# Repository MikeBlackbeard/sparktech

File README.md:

# sparktech Group for Hardware Engineering and Embedded Systems

## Team Members
1. Miguel
2. Nur
3. Wen
4. Vincent

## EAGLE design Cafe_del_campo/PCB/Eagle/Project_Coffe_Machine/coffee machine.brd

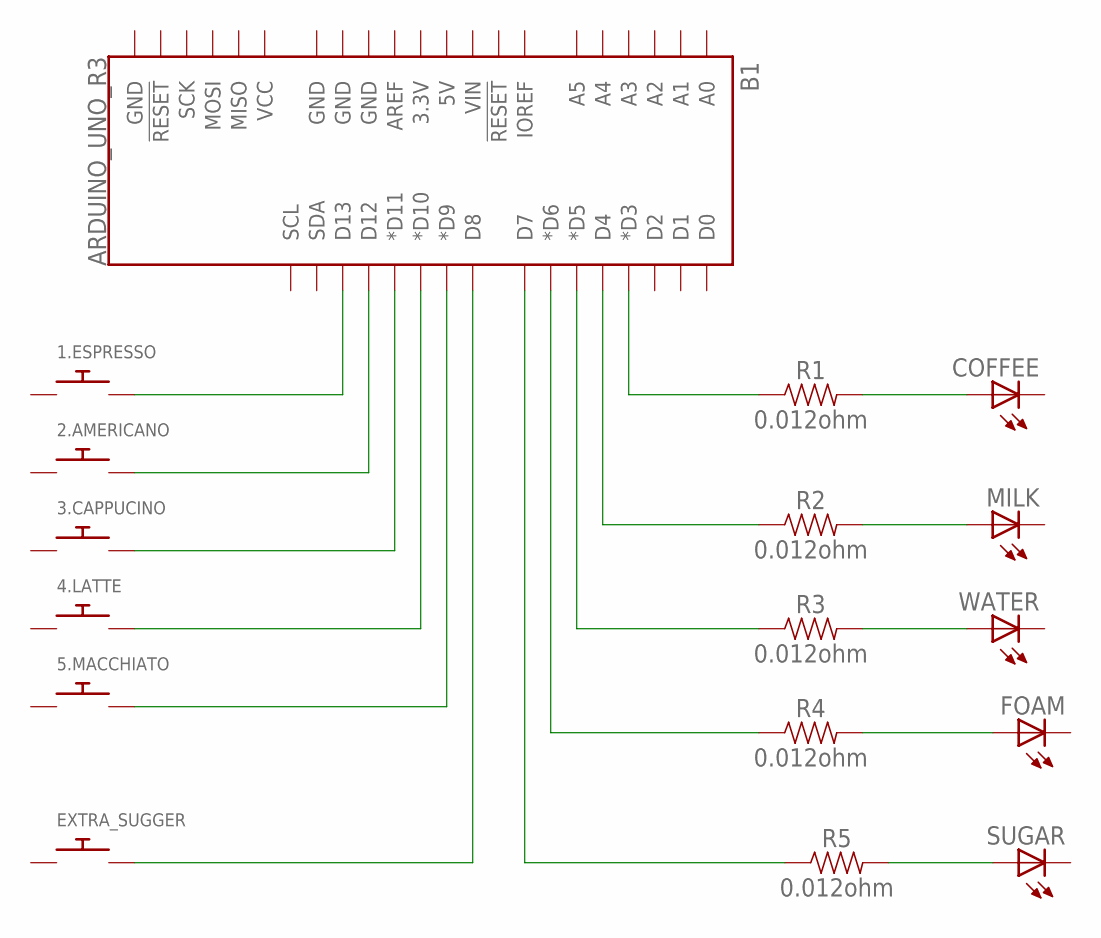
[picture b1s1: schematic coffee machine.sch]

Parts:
1.ESPRESSO, 2.AMERICANO, 3.CAPPUCINO, 4.LATTE, 5.MACCHIATO: SWITCH_PUSHBUTTONEVQ-PE; TACT_PANA-EVQ
B1: ARDUINO_UNO_R3; ARDUINO_R3
COFFEE: LED3MM
EXTRA_SUGGER: SWITCH_PUSHBUTTONEVQ-PE; TACT_PANA-EVQ
FOAM: LED3MM
MILK: LED3MM
R1, R2, R3, R4, R5: 0.012ohm; 0603
SUGAR: LED3MM
WATER: LED3MM

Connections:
unnamed: 1.ESPRESSO.P$2, B1.D13
unnamed: 2.AMERICANO.P$2, B1.D12
unnamed: 3.CAPPUCINO.P$2, B1.D11 (*D11)
unnamed: 4.LATTE.P$2, B1.D10 (*D10)
unnamed: 5.MACCHIATO.P$2, B1.D9 (*D9)
unnamed: B1.D8, EXTRA_SUGGER.P$2
unnamed: B1.D7, R5.1
unnamed: B1.D6 (*D6), R4.1
unnamed: B1.D5 (*D5), R3.1
unnamed: B1.D4, R2.1
unnamed: B1.D3 (*D3), R1.1
unnamed: COFFEE.A, R1.2
unnamed: MILK.A, R2.2
unnamed: R3.2, WATER.A
unnamed: FOAM.A, R4.2
unnamed: R5.2, SUGAR.A

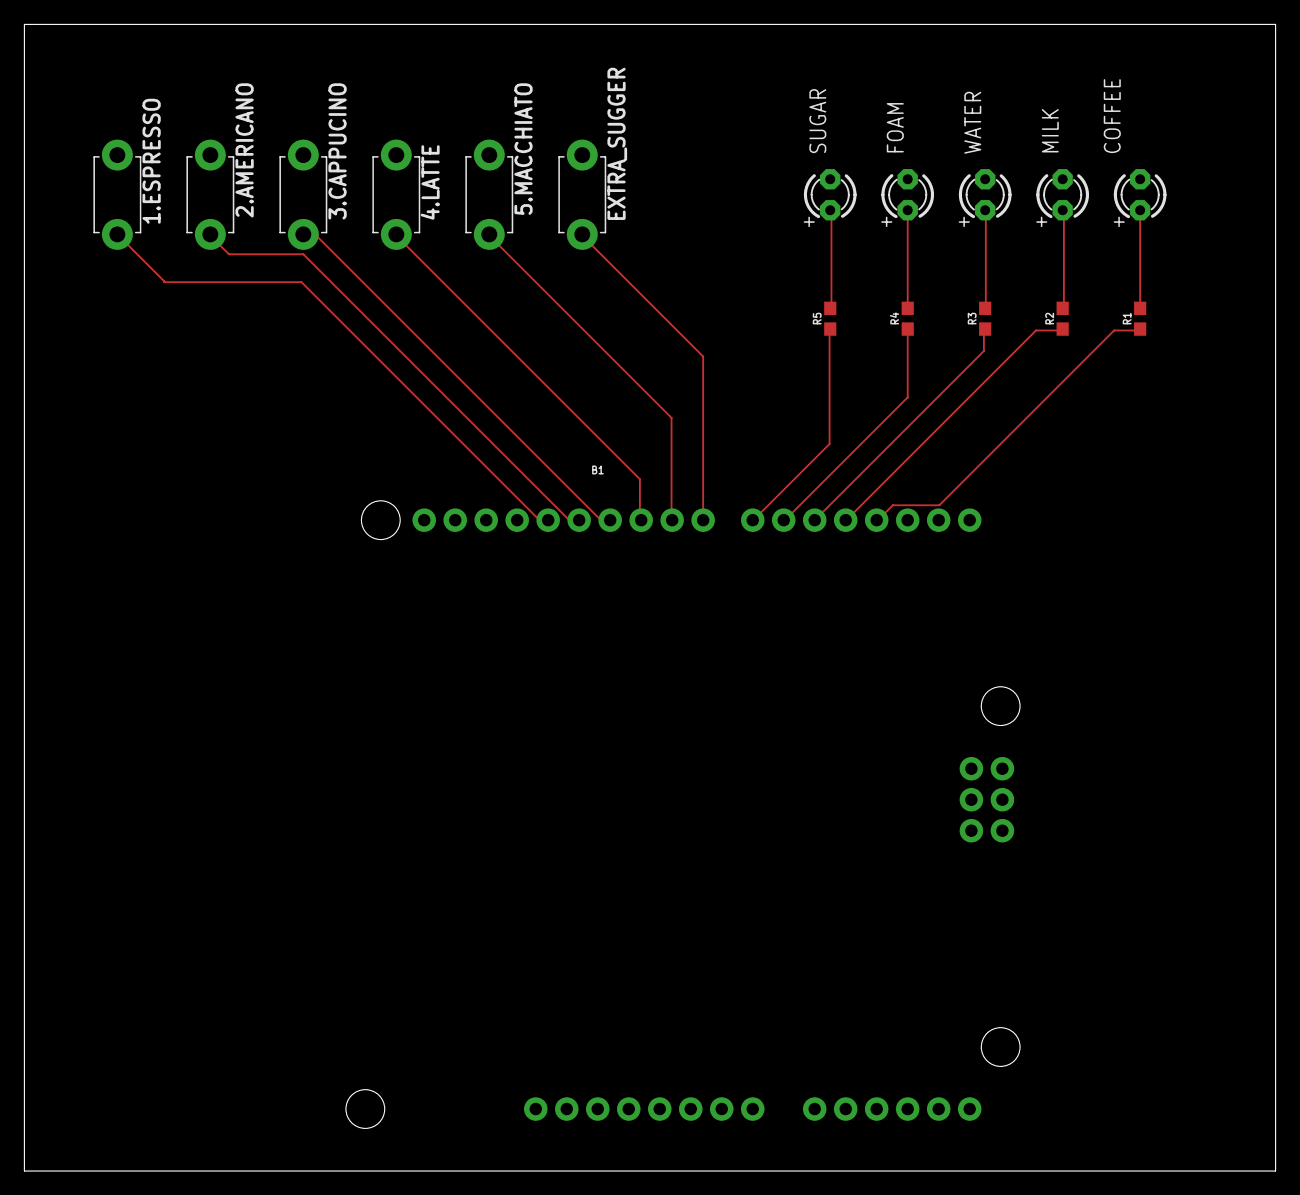
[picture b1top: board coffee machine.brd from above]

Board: 2 copper layers, 102.5 x 94.0 mm, 17 parts (0 on the bottom side), 16 nets.

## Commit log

2022-05-12 VHDL
2022-05-12 ReadMe Update
2022-05-17 Used components and descriptions
2022-05-26 Create graphs and figures
2022-05-26 Diagrams
2022-05-26 coffee ratio
2022-06-22 Documents added
2022-06-23 Eagle Added and folder organized
2022-06-23 document
2022-06-24 update of the Xilinx file
2022-06-24 EyeOfMordor documentaion
2022-06-24 documentations
2022-06-28 Presentation file
    Presentation is uploaded

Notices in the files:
parts and their libraries:
SparkFun-Boards: Licensing: Creative Commons ShareAlike 4.0 International - https://creativecommons.org/licenses/by-sa/4.0
